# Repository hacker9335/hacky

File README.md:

# Hacky
A custom mechanical macropad built on the Seeed XIAO RP2040, running QMK/VIA firmware.
Features

Seeed XIAO RP2040 — QMK/VIA compatible
4 mechanical keys
2 rotary encoders (volume/scroll/custom functions)
OLED display for
3D printed 3-part case with an angled stand

Bill of Materials

| Component | Qty |
|-----------|-----|
| RP2040 (XIAO) | 1 |
| Switches | 4 |
| Encoders | 2 |
| OLED| 1 |
| PCB | 1 |

PCB

Schematic

Case

Altogether

i made the case kinda bare cus i own a 3d printer and im planning to make a seperate top for it after it arrives so it can be a bit more accurate

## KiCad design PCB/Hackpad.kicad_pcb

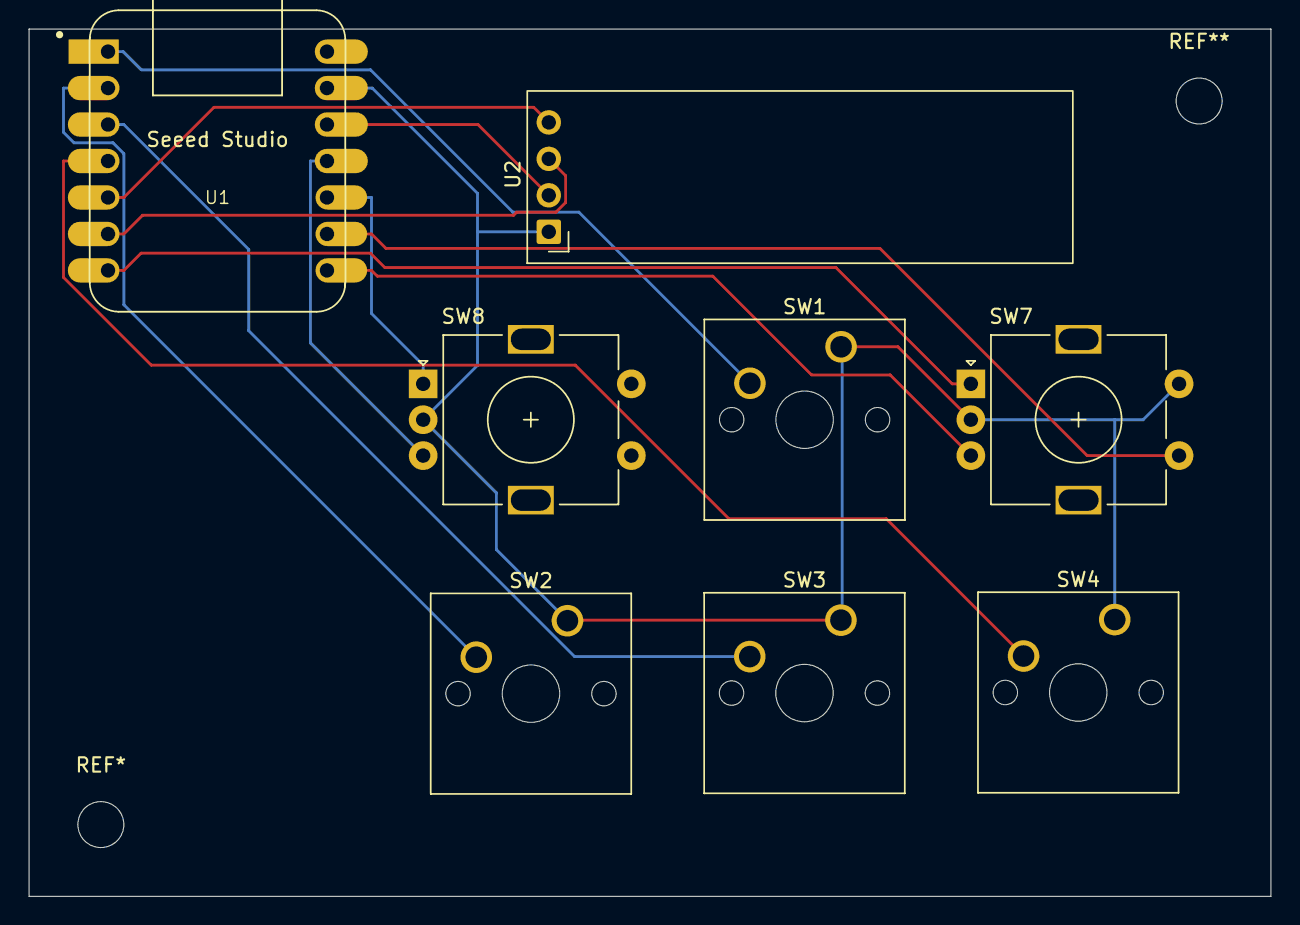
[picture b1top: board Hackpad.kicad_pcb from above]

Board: 2 copper layers, 86.5 x 60.4 mm, 8 parts (0 on the bottom side), 13 nets.

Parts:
SW1, SW2, SW3, SW4: SW_Push; SW_Cherry_MX_1.00u_PCB
SW7, SW8: RotaryEncoder_Switch; RotaryEncoder_Alps_EC11E-Switch_Vertical_H20mm
U1: MOUDLE-SEEEDUINO-XIAO; XIAO-Generic-Hybrid-14P-2.54-21X17.8MM
U2: ER_OLEDM0.91_1x-I2C

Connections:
unnamed: U1.12 (3V3), U2.2 (VCC)
unnamed: SW1.1, SW2.1, SW3.1, SW4.1, SW7.C, SW7.S2, SW8.C, U1.13 (GND), U2.1 (GND)
unnamed: SW1.2, U1.1 (PA02_A0_D0)
unnamed: SW2.2, U1.2 (PA4_A1_D1)
unnamed: SW8.A, U1.10 (PA5_A9_D9_MISO)
unnamed: SW8.B, U1.11 (PA6_A10_D10_MOSI)
unnamed: SW7.S1, U1.9 (PA7_A8_D8_SCK)
unnamed: U1.5 (PA8_A4_D4_SDA), U2.4 (SDA)
unnamed: U1.6 (PA9_A5_D5_SCL), U2.3 (SCL)
unnamed: SW3.2, U1.3 (PA10_A2_D2)
unnamed: SW4.2, U1.4 (PA11_A3_D3)
unnamed: SW7.A, U1.7 (PB08_A6_D6_TX)
unnamed: SW7.B, U1.8 (PB09_A7_D7_RX)

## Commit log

2026-06-19 Enhance README with project details and images
    Added detailed description of the macropad project, including features and images.
2026-06-20 Remove Hackpad from repository
2026-06-20 Revise README for macropad project details
    Updated README to provide detailed information about the custom macropad, including features, bill of materials, and images.
